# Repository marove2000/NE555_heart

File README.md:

# Heart SMD NE555
24 LEDs forming a LED-Heart driven by a NE555 bistable vibrator. A LED-Light runs around the heart. The speed of the running LED-light can be modified by changeing some resistors.
This soldering Kit requires first experience in SMD-Soldering and is a very good practice for the size 0805.

- Status: **Complete**
- Difficulty: **3/5**

### Parts List

| Description                   |  Name  | Quantity |
|-------------------------------|:------:|:--------:|
| SMD LED 0805 red              | D5-D28 |    24    |
| SMD Capacitor 1uF             |   C1   |     1    |
| SMD Capacitor 100n            |  C2,C3 |     2    |
| SMD Diode 1N4007              |  D1-D4 |     4    |
| SMD Push Button               |   SW1  |     1    |
| SMD Resistor 0805 47k         |   R1   |     1    |
| SMD Resistor 0805 1k          |   R2   |     1    |
| SMD Resistor 0805 100k        |  R3,R4 |     2    |
| SMD Resistor 0805 47R         |   R5   |     1    |
| NE555 SOIC-8                  |   U1   |     1    |
| CD4017 SOP-16                 |  U2-U4 |     3    |
| CR2032 Battery Holder (SMD)   |   BT1  |     1    |
| CR2032 Battery (not included) |        |     1    |

### Manual
You can find the manual and pictures of every step here: https://github.com/Binary-Kitchen/SolderingTutorial

### Copyright and Authorship

- Board: [CC-BY-SA 4.0](https://creativecommons.org/licenses/by-sa/4.0/) - Timo Schindler, Thomas Schmid
- CR2032 battery holder footprint: [CC-BY 4.0](https://creativecommons.org/licenses/by/4.0/) - Sparkfun (https://github.com/sparkfun/SparkFun-KiCad-Libraries)

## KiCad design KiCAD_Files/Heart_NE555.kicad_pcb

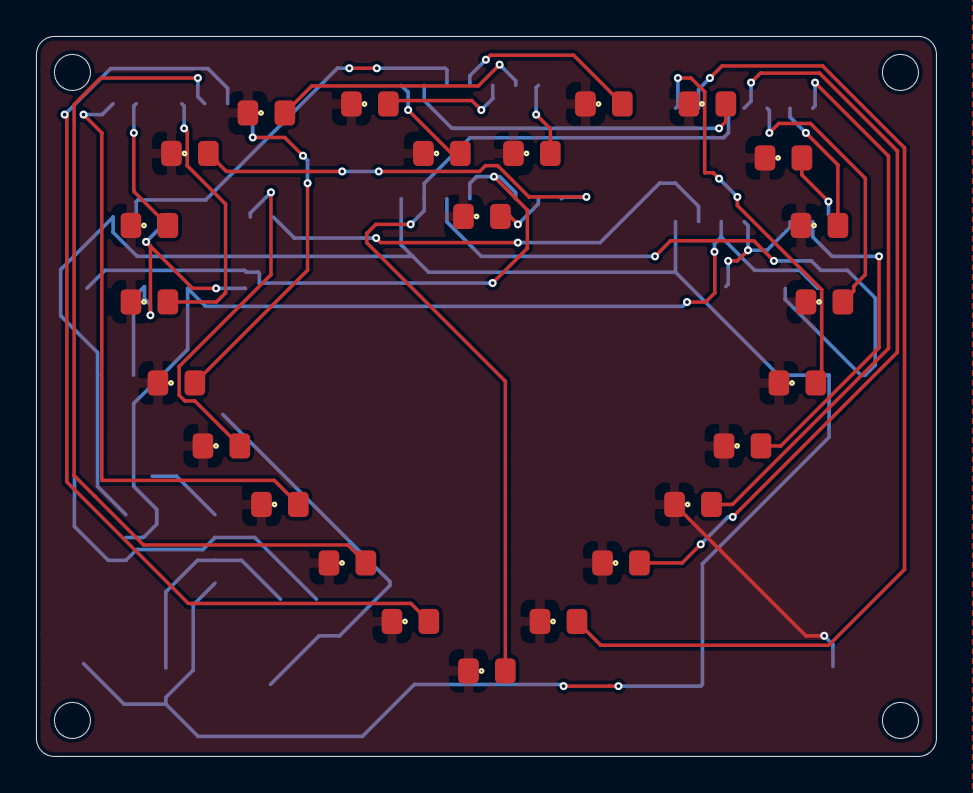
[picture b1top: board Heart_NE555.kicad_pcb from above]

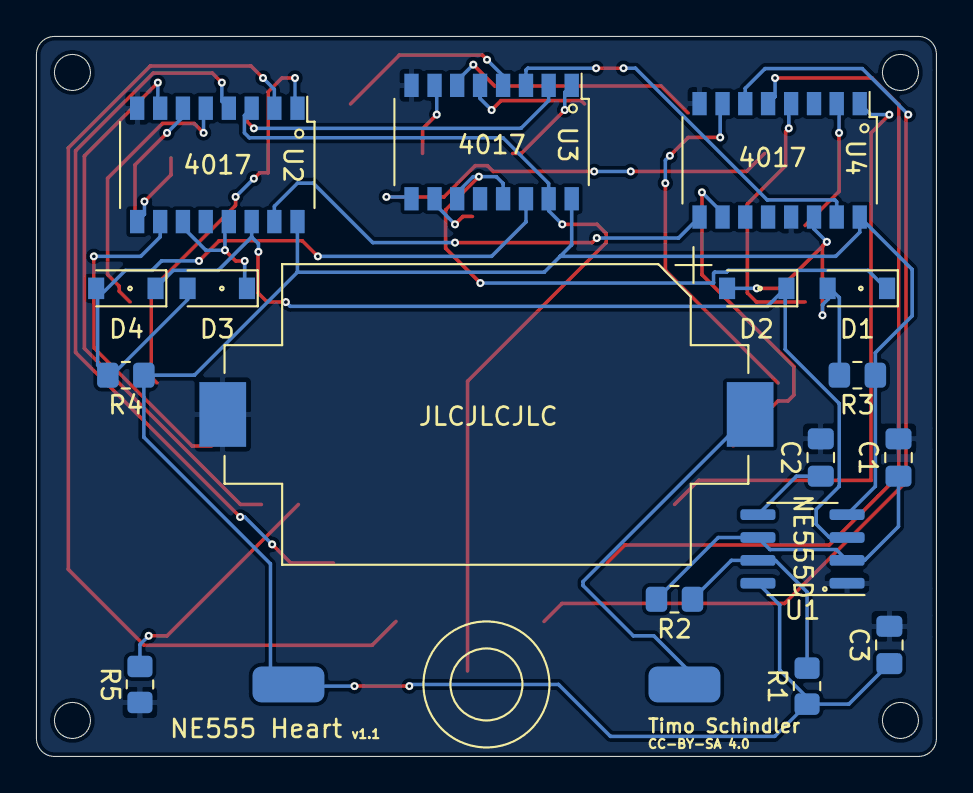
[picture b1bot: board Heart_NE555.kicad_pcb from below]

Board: 2 copper layers, 50.0 x 40.0 mm, 43 parts (18 on the bottom side), 38 nets.

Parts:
BT1: Battery_Cell; BatteryHolder_Keystone_1060_1x2032
C1: 1µ; C_0805_2012Metric_Pad1.18x1.45mm_HandSolder
C2, C3: 100n; C_0805_2012Metric_Pad1.18x1.45mm_HandSolder
D1, D2, D3, D4: 1N4007; D_SOD-123
D5, D6, D7, D8, D9, D10, D11, D12, D13, D14, D15, D16, D17, D18, D19, D20, D21, D22, D23, D24, D25, D26, D27, D28: LED; LED_0805_2012Metric_Pad1.15x1.40mm_HandSolder
R1: 47k; R_0805_2012Metric_Pad1.20x1.40mm_HandSolder
R2: 1k; R_0805_2012Metric_Pad1.20x1.40mm_HandSolder
R3, R4: 100k; R_0805_2012Metric_Pad1.20x1.40mm_HandSolder
R5: 47R; R_0805_2012Metric_Pad1.20x1.40mm_HandSolder
Ref**: Val**; heart_small
SW1: SW_DIP_x01; Push_Button
U1: NE555D; SOIC-8_3.9x4.9mm_P1.27mm
U2, U3, U4: 4017; SOP-16_4.4x10.4mm_P1.27mm

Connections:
+3V0: BT1.1, SW1.1
/Common-R: D5.1, D6.1, D7.1, D8.1, D9.1, D10.1, D11.1, D12.1, D13.1, D14.1, D15.1, D16.1, D17.1, D18.1, D19.1, D20.1, D21.1, D22.1, D23.1, D24.1, D25.1, D26.1, D27.1, D28.1, R5.2
GND: BT1.2, C1.2, C2.2, C3.2, R5.1, U1.1, U2.8, U3.8, U4.8, U4.13
unnamed: C1.1, R2.2, U1.2, U1.6
unnamed: C2.1, U1.5
unnamed: D1.1, U3.11, U3.13
unnamed: D1.2, D2.2, R3.2, U4.14
unnamed: D2.1, D4.1, U1.3, U2.14
unnamed: D3.1, U2.11, U2.13
unnamed: D3.2, D4.2, R4.2, U3.14
unnamed: D5.2, U2.3, U3.15
unnamed: D6.2, U2.2
unnamed: D7.2, U2.4
unnamed: D8.2, U2.7
unnamed: D9.2, U2.10
unnamed: D10.2, U2.1
unnamed: D11.2, U2.5
unnamed: D12.2, U2.6
unnamed: D13.2, U2.9
unnamed: D14.2, U3.2
unnamed: D15.2, U3.4
unnamed: D16.2, U3.7
unnamed: D17.2, U3.10
unnamed: D18.2, U3.1
unnamed: D19.2, U3.5
unnamed: D20.2, U3.6
unnamed: D21.2, U3.9
unnamed: D22.2, U4.2
unnamed: D23.2, U4.4
unnamed: D24.2, U4.7
unnamed: D25.2, U4.10
unnamed: D26.2, U4.1
unnamed: D27.2, U4.5
unnamed: D28.2, U4.6
unnamed: R1.2, R2.1, U1.7
unnamed: U2.15, U4.9
unnamed: U3.3, U4.15
VCC: C3.1, R1.1, R3.1, R4.1, SW1.2, U1.4, U1.8, U2.16, U3.16, U4.16

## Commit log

2021-01-21 inital commit
2021-01-23 fixed an naming error
2021-01-23 added gerber-files
2021-05-22 modified push button footprint
2021-05-22 changed footprints of diodes, fixed last-led-bug
2021-05-22 generated new gerberfiles
2021-05-22 increased version number, minor changes
2021-05-22 generated new gerber fiels
2021-05-22 added license-file
2021-05-22 created readme with bom
